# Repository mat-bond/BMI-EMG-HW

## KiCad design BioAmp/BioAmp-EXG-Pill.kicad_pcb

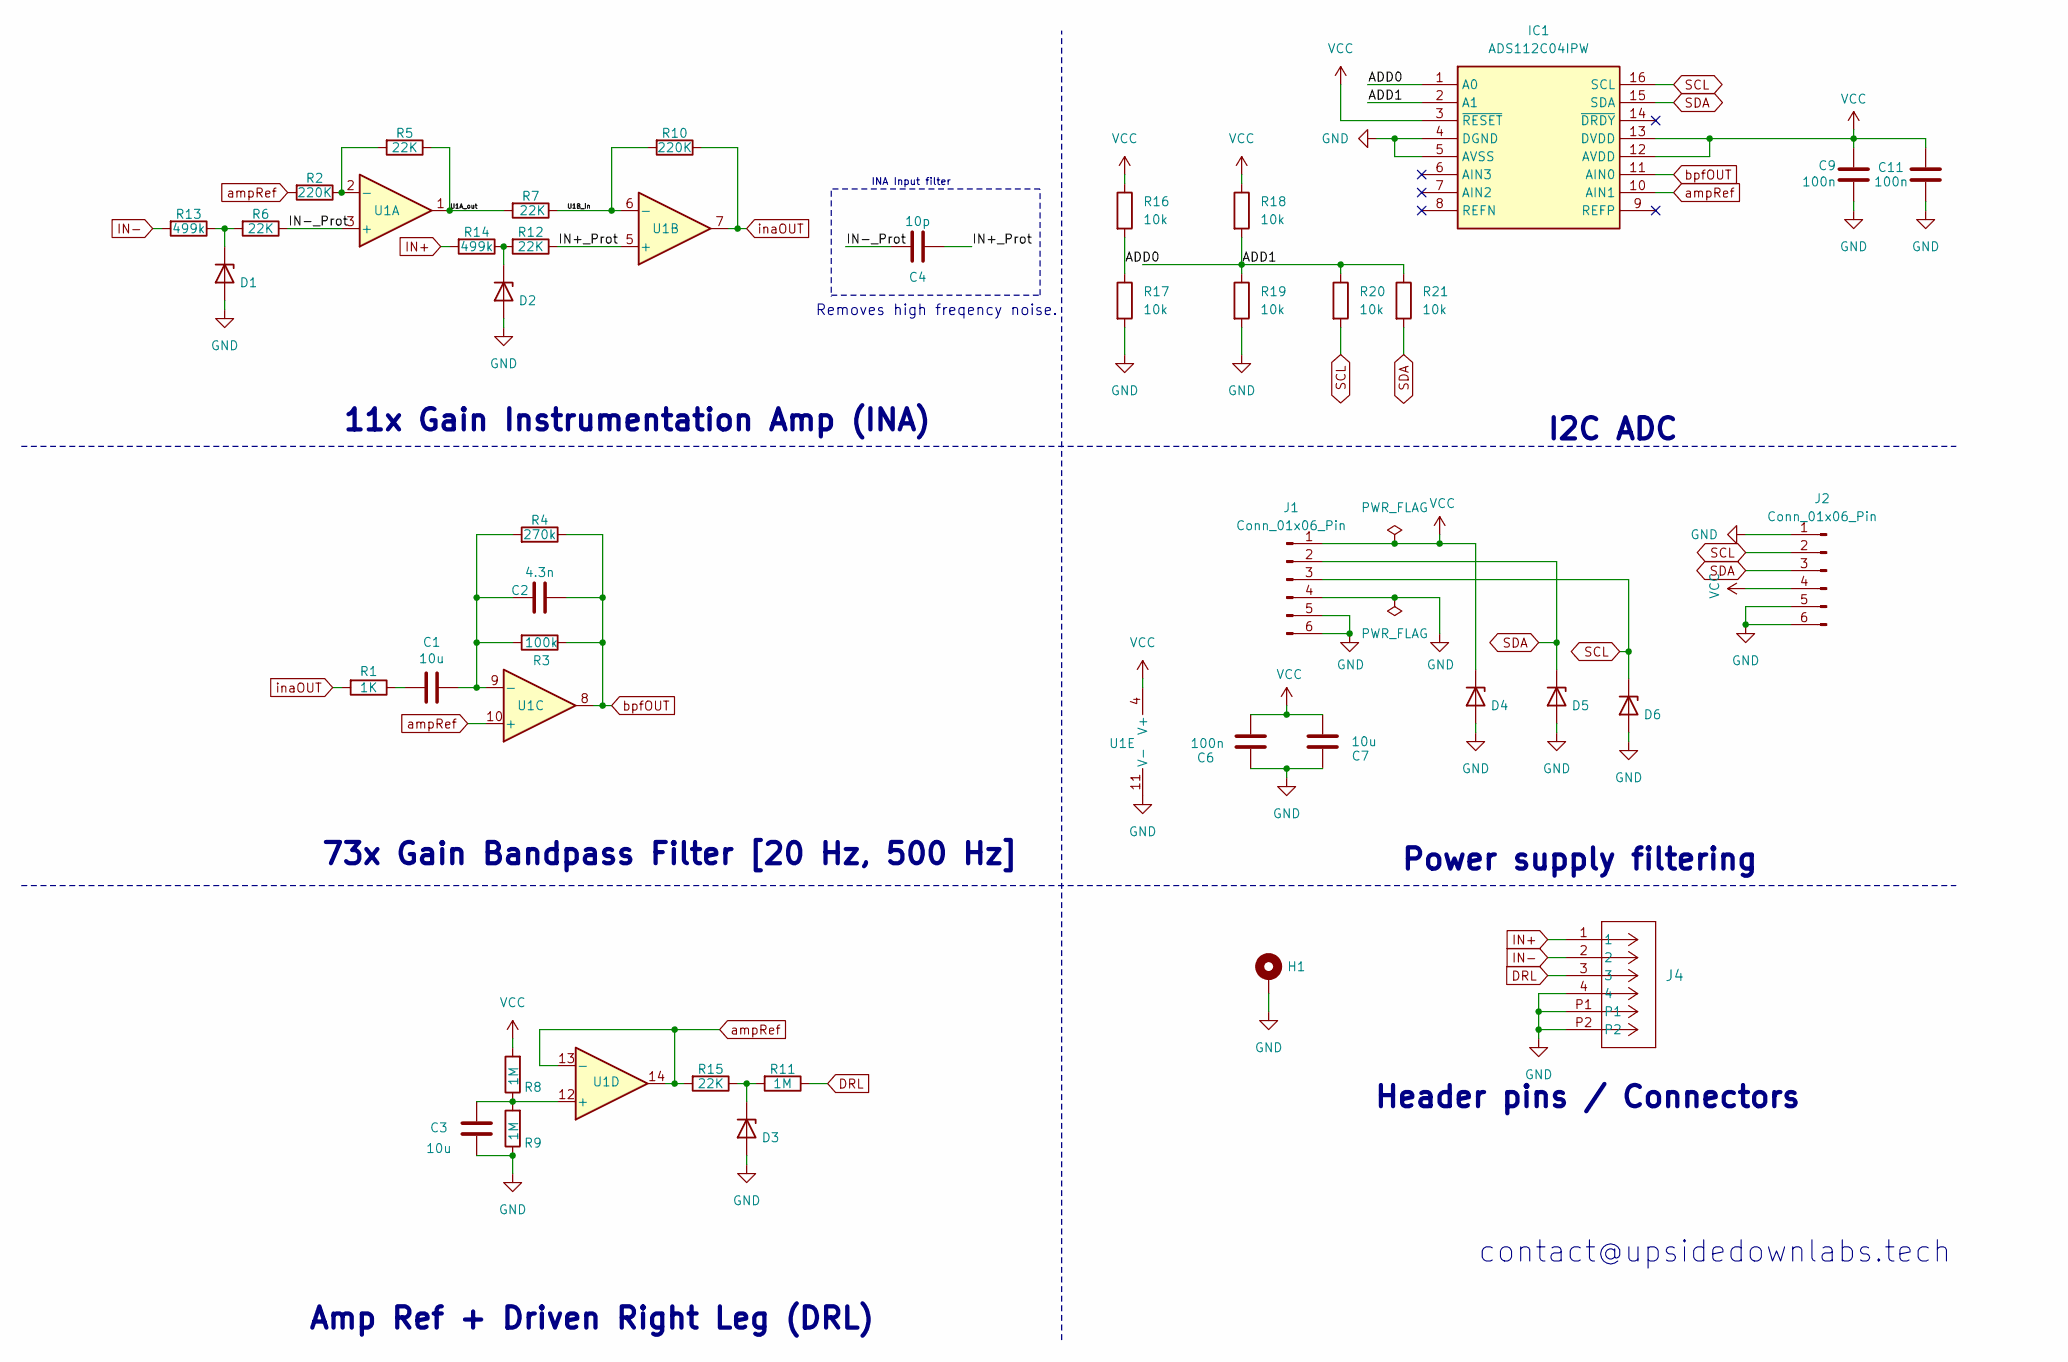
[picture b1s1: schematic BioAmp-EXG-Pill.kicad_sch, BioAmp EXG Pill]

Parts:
C1, C3, C7: 10u; C_0603_1608Metric_Pad1.08x0.95mm_HandSolder
C2: 4.3n; C_0603_1608Metric_Pad1.08x0.95mm_HandSolder
C4: 10p; C_0603_1608Metric_Pad1.08x0.95mm_HandSolder
C6: 100n; C_0603_1608Metric_Pad1.08x0.95mm_HandSolder
C9, C11: 100n; C_0402_1005Metric
D1, D2, D3, D4, D5, D6: ESD441DPLR; D_0201_0603Metric
H1: MountingHole_Pad; MountingHole_2.5mm_Pad
IC1: ADS112C04IPW; SOP65P640X120-16N; Mouser Part Number 595-ADS112C04IPW
J1, J2: Conn_01x06_Pin; CONN_5037630000-SD_04_MOL
J4: 522710469; CON_522710469_MOL
R1: 1K; R_0603_1608Metric_Pad0.98x0.95mm_HandSolder
R2, R10: 220K; R_0603_1608Metric_Pad0.98x0.95mm_HandSolder
R3: 100k; R_0603_1608Metric_Pad0.98x0.95mm_HandSolder
R4: 270k; R_0603_1608Metric_Pad0.98x0.95mm_HandSolder
R5, R6, R7, R12, R15: 22K; R_0603_1608Metric_Pad0.98x0.95mm_HandSolder
R8, R9, R11: 1M; R_0603_1608Metric_Pad0.98x0.95mm_HandSolder
R13, R14: 499k; R_0603_1608Metric_Pad0.98x0.95mm_HandSolder
R16, R17, R18, R19, R20, R21: 10k; R_0603_1608Metric_Pad0.98x0.95mm_HandSolder
U1: TL074HIPWR; TSSOP-14_4.4x5mm_P0.65mm

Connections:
/ADD0: IC1.1 (A0), R16.2, R17.1
/ADD1: IC1.2 (A1), R18.2, R19.1, R20.1, R21.1
/IN+_Prot: C4.1, R12.1, U1.5 (+)
/IN-_Prot: C4.2, R6.1, U1.3 (+)
/U1A_out: R5.1, R7.2, U1.1
/U1B_in: R7.1, R10.2, U1.6 (-)
DRL: J4.3, R11.1
GND: C3.2, C6.1, C7.1, C9.1, C11.1, D1.2 (A), D2.2 (A), D3.2 (A), D4.2 (A), D5.2 (A), D6.2 (A), H1.1 (1_1), IC1.4 (DGND), IC1.5 (AVSS), J1.4, J1.5, J1.6, J2.1, J2.5, J2.6, J4.4, J4.P1, J4.P2, R9.1, R17.2, R19.2, U1.11 (V-)
IN+: J4.1, R14.2
IN-: J4.2, R13.2
unnamed: C1.2, R1.1
unnamed: D1.1 (K), R6.2, R13.1
unnamed: D2.1 (K), R12.2, R14.1
unnamed: D3.1 (K), R11.2, R15.1
unnamed: R2.1, R5.2, U1.2 (-)
unnamed: C1.1, C2.2, R3.2, R4.2, U1.9 (-)
unnamed: C3.1, R8.1, R9.2, U1.12 (+)
SCL: D6.1 (K), IC1.16 (SCL), J1.3, J2.2, R20.2
SDA: D5.1 (K), IC1.15 (SDA), J1.2, J2.3, R21.2
VCC: C6.2, C7.2, C9.2, C11.2, D4.1 (K), IC1.3 (~RESET), IC1.12 (AVDD), IC1.13 (DVDD), J1.1, J2.4, R8.2, R16.1, R18.1, U1.4 (V+)
ampRef: IC1.10 (AIN1), R2.2, R15.2, U1.10 (+), U1.13 (-), U1.14
bpfOUT: C2.1, IC1.11 (AIN0), R3.1, R4.1, U1.8
inaOUT: R1.2, R10.1, U1.7

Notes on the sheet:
contact@upsidedownlabs.tech
73x Gain Bandpass Filter [20 Hz, 500 Hz]
Header pins / Connectors
11x Gain Instrumentation Amp (INA)
Power supply filtering
Amp Ref + Driven Right Leg (DRL)
Removes high freqency noise.
I2C ADC
INA Input filter

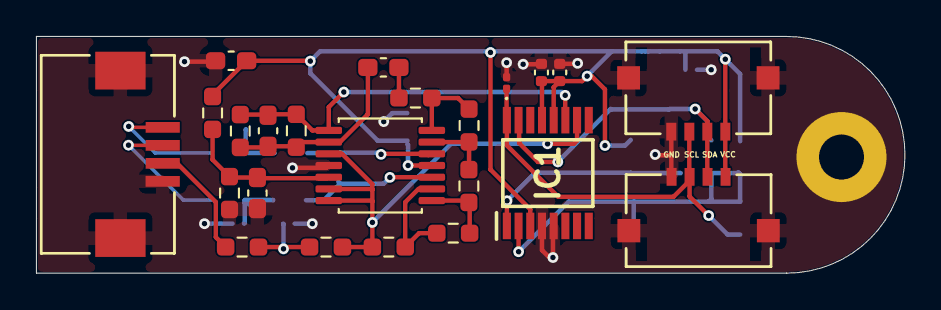
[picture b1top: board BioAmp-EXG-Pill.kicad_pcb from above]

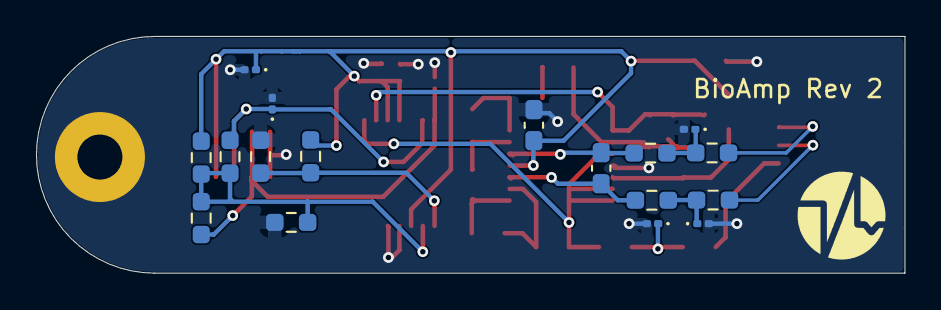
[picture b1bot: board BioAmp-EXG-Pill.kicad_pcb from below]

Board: 4 copper layers, 48.2 x 13.2 mm, 41 parts (17 on the bottom side), 23 nets.
